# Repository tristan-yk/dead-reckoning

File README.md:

# Inertial State Estimation

https://github.com/user-attachments/assets/70ce5969-a767-4737-bc72-2eb9b916396b

This is an online attitude and altitude estimator built around an extended Kalman filter. The filter is written and tested in MATLAB and Simulink against a simulated plant, then generated to single-precision C with MATLAB Coder and run on an STM32G4 Nucleo with a custom sensor shield. It does not estimate horizontal position. Nothing on the board observes it, so the only way to get it would be double-integrating acceleration, and that drifts without bound.

There are ten states: an orientation quaternion, a three-axis gyroscope bias, and a vertical channel of acceleration, velocity and altitude. The gyroscope propagates orientation forward and three measurements correct it. The accelerometer gives a gravity reference for roll and pitch, the magnetometer gives heading once local declination is applied, and the barometer gives altitude through the standard atmosphere model. Gravity is only worth trusting when the device is not accelerating, so accelerometer corrections to attitude get dropped whenever specific force is more than ten percent off *g*. The same sample still drives the vertical acceleration state. All of this is tested first against a Simulink plant with rigid-body motion, sensor noise and bias, and an earth magnetic field model.

The firmware runs a 100 Hz tick and spends about 1.5 ms of each 10 ms period inside the generated filter. The BNO055 is read in raw AMG mode, so fusion happens in the filter rather than in the sensor. The BMP390 runs at x32 oversampling, which holds its noise near 0.9 Pa. Three buttons move the board between idle, calibration and running, with status shown on a small OLED, and the whole state goes out over serial every tick to a browser dashboard that draws the device in a north-fixed frame.

## Repository

- Simulation/EKF - filter math, parameters, and the code generation entry point
- Simulation/Plant - Simulink plant and sensor models
- Simulation/Codegen - generated C for the filter
- Firmware - STM32 application and device drivers
- Electrical - KiCad schematic, PCB, and fabrication outputs for the shield
- Scripts - build, flash, and source sync helpers, plus the live dashboard

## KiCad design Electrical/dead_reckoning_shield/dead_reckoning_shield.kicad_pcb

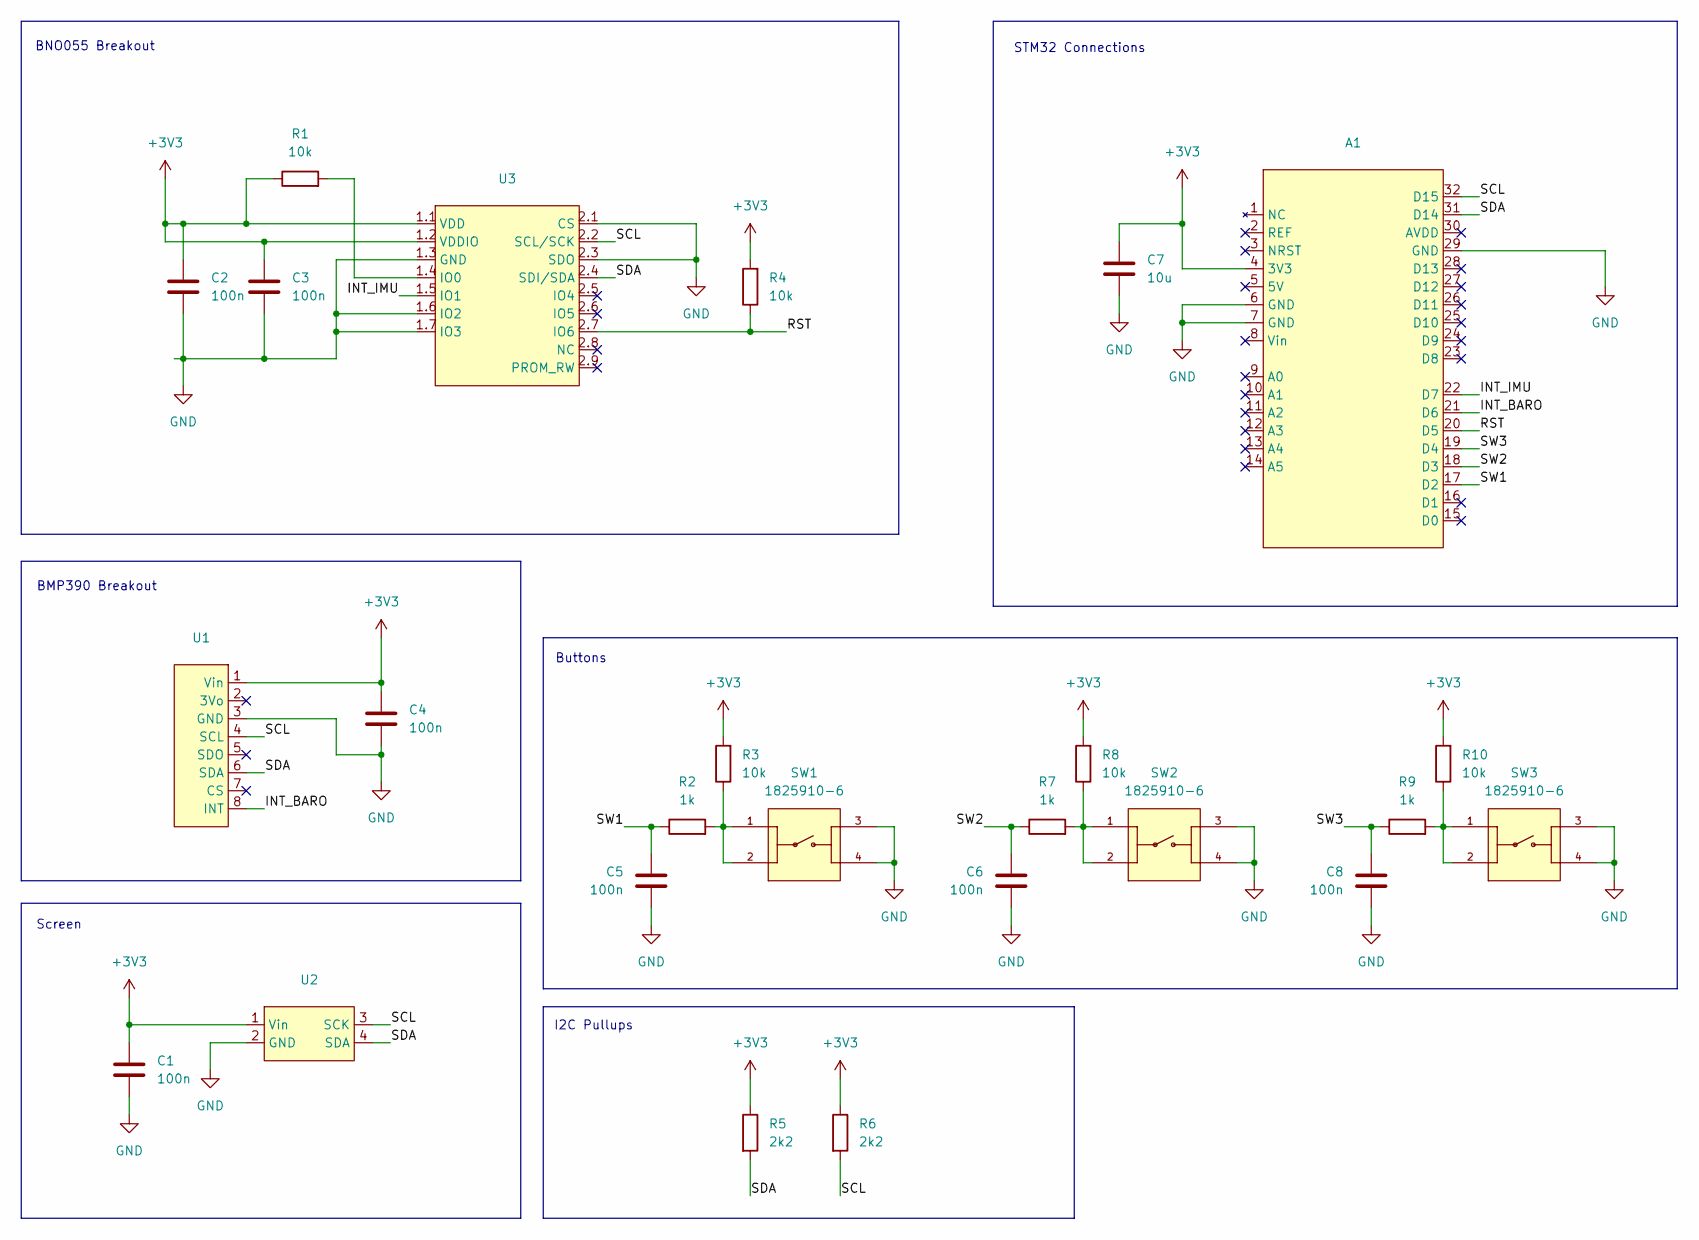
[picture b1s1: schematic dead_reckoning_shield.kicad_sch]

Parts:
A1: STM32_Shield
C1, C2, C3, C4, C5, C6, C8: 100n; C_0603_1608Metric_Pad1.08x0.95mm_HandSolder
C7: 10u; C_0805_2012Metric_Pad1.18x1.45mm_HandSolder
R1, R3, R4, R8, R10: 10k; R_0603_1608Metric_Pad0.98x0.95mm_HandSolder
R2, R7, R9: 1k; R_0603_1608Metric_Pad0.98x0.95mm_HandSolder
R5, R6: 2k2; R_0603_1608Metric_Pad0.98x0.95mm_HandSolder
SW1, SW2, SW3: 1825910-6; SW_1825910-6-4; PARTREV C10
U1: BMP390
U2: Screen
U3: BNO055

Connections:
+3V3: A1.4 (3V3), C1.1, C2.1, C3.1, C4.1, C7.1, R1.1, R3.2, R4.2, R5.1, R6.1, R8.2, R10.2, U1.1 (Vin), U2.1 (Vin), U3.1.1 (VDD), U3.1.2 (VDDIO)
/INT_BARO: A1.21 (D6), U1.8 (INT)
/INT_IMU: A1.22 (D7), U3.1.5 (IO1)
/RST: A1.20 (D5), R4.1, U3.2.7 (IO6)
/SCL: A1.32 (D15), R6.2, U1.4 (SCL), U2.3 (SCK), U3.2.2 (SCL/SCK)
/SDA: A1.31 (D14), R5.2, U1.6 (SDA), U2.4 (SDA), U3.2.4 (SDI/SDA)
/SW1: A1.17 (D2), C5.1, R2.1
/SW2: A1.18 (D3), C6.1, R7.1
/SW3: A1.19 (D4), C8.1, R9.1
GND: A1.6 (GND), A1.7 (GND), A1.29 (GND), C1.2, C2.2, C3.2, C4.2, C5.2, C6.2, C7.2, C8.2, SW1.3, SW1.4, SW2.3, SW2.4, SW3.3, SW3.4, U1.3 (GND), U2.2 (GND), U3.1.3 (GND), U3.1.6 (IO2), U3.1.7 (IO3), U3.2.1 (CS), U3.2.3 (SDO)
unnamed: R2.2, R3.1, SW1.1, SW1.2
unnamed: R7.2, R8.1, SW2.1, SW2.2
unnamed: R9.2, R10.1, SW3.1, SW3.2
unnamed: R1.2, U3.1.4 (IO0)

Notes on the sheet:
Screen
STM32 Connections
I2C Pullups
BMP390 Breakout
Buttons
BNO055 Breakout

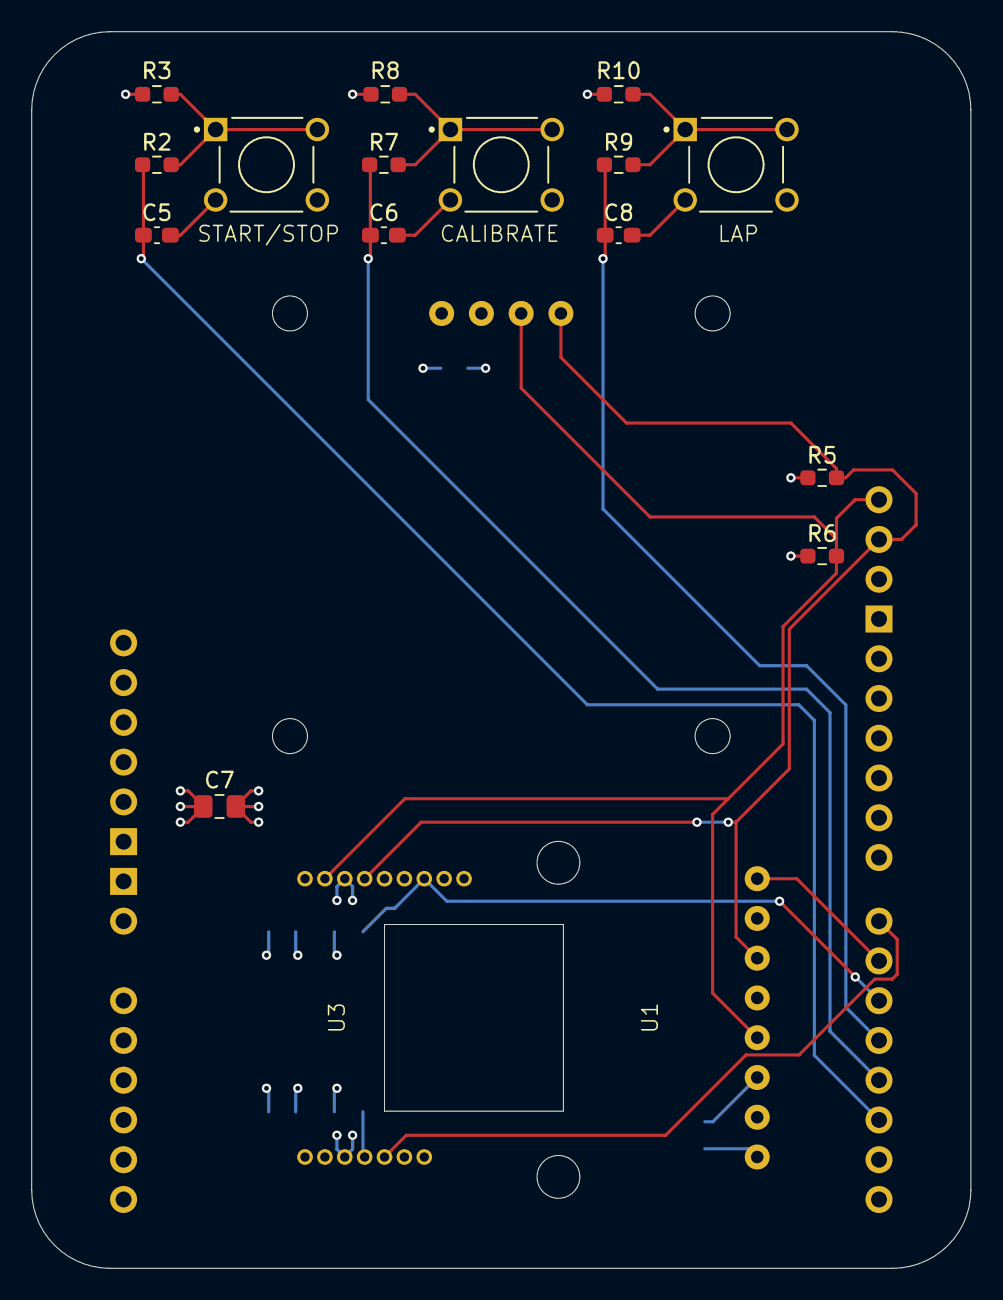
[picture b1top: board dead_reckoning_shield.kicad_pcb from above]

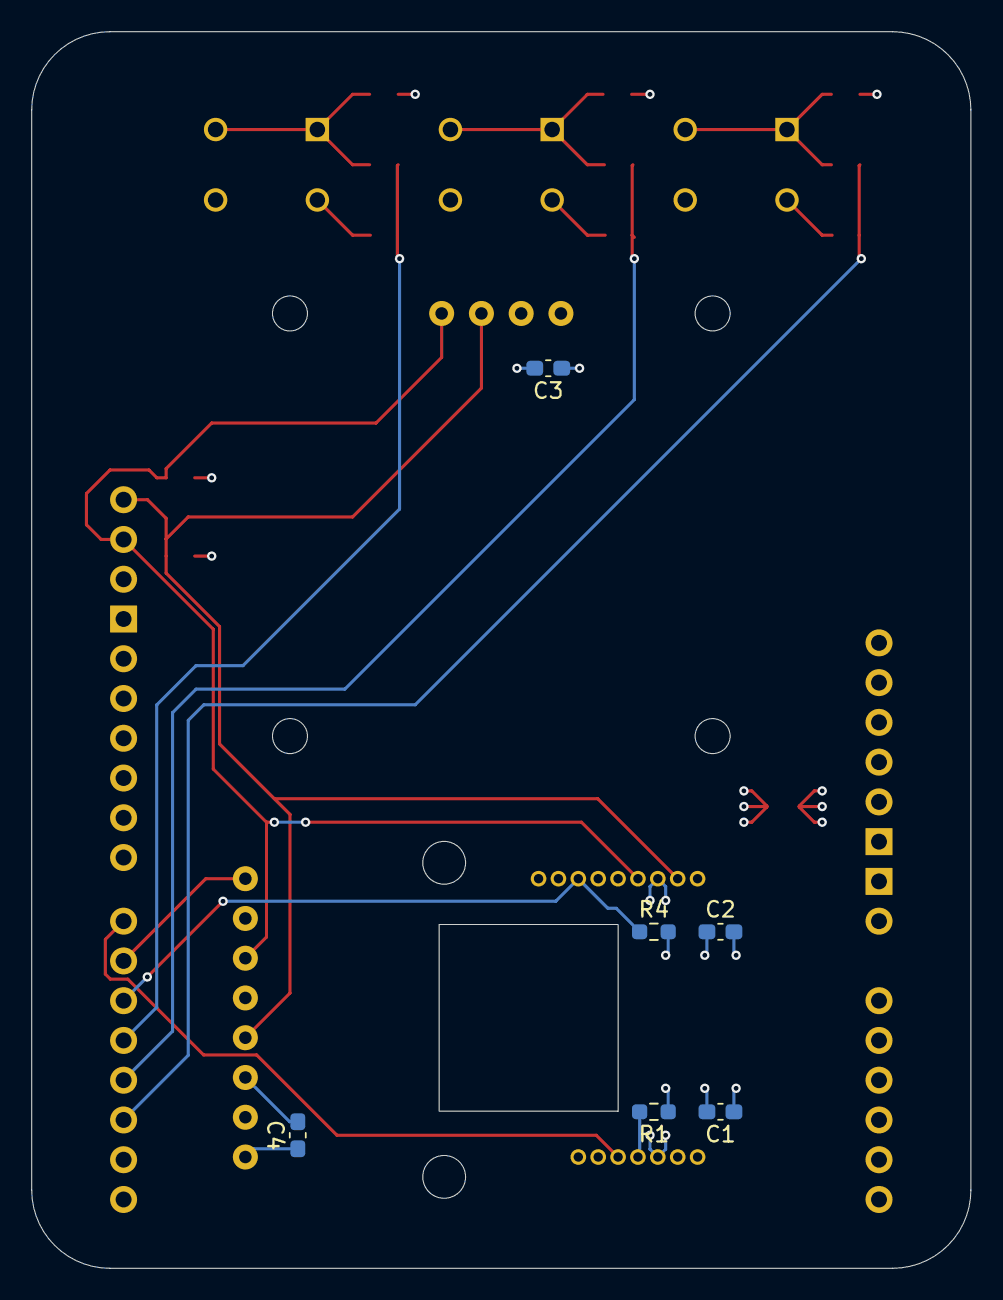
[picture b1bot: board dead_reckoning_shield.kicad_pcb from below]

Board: 4 copper layers, 60.0 x 79.0 mm, 25 parts (6 on the bottom side), 14 nets.

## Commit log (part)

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2025-12-14 Finished Electrical Design
2025-12-14 sensor initialization and test
2025-12-19 Added test firmware
2026-03-05 preliminary sim setup
